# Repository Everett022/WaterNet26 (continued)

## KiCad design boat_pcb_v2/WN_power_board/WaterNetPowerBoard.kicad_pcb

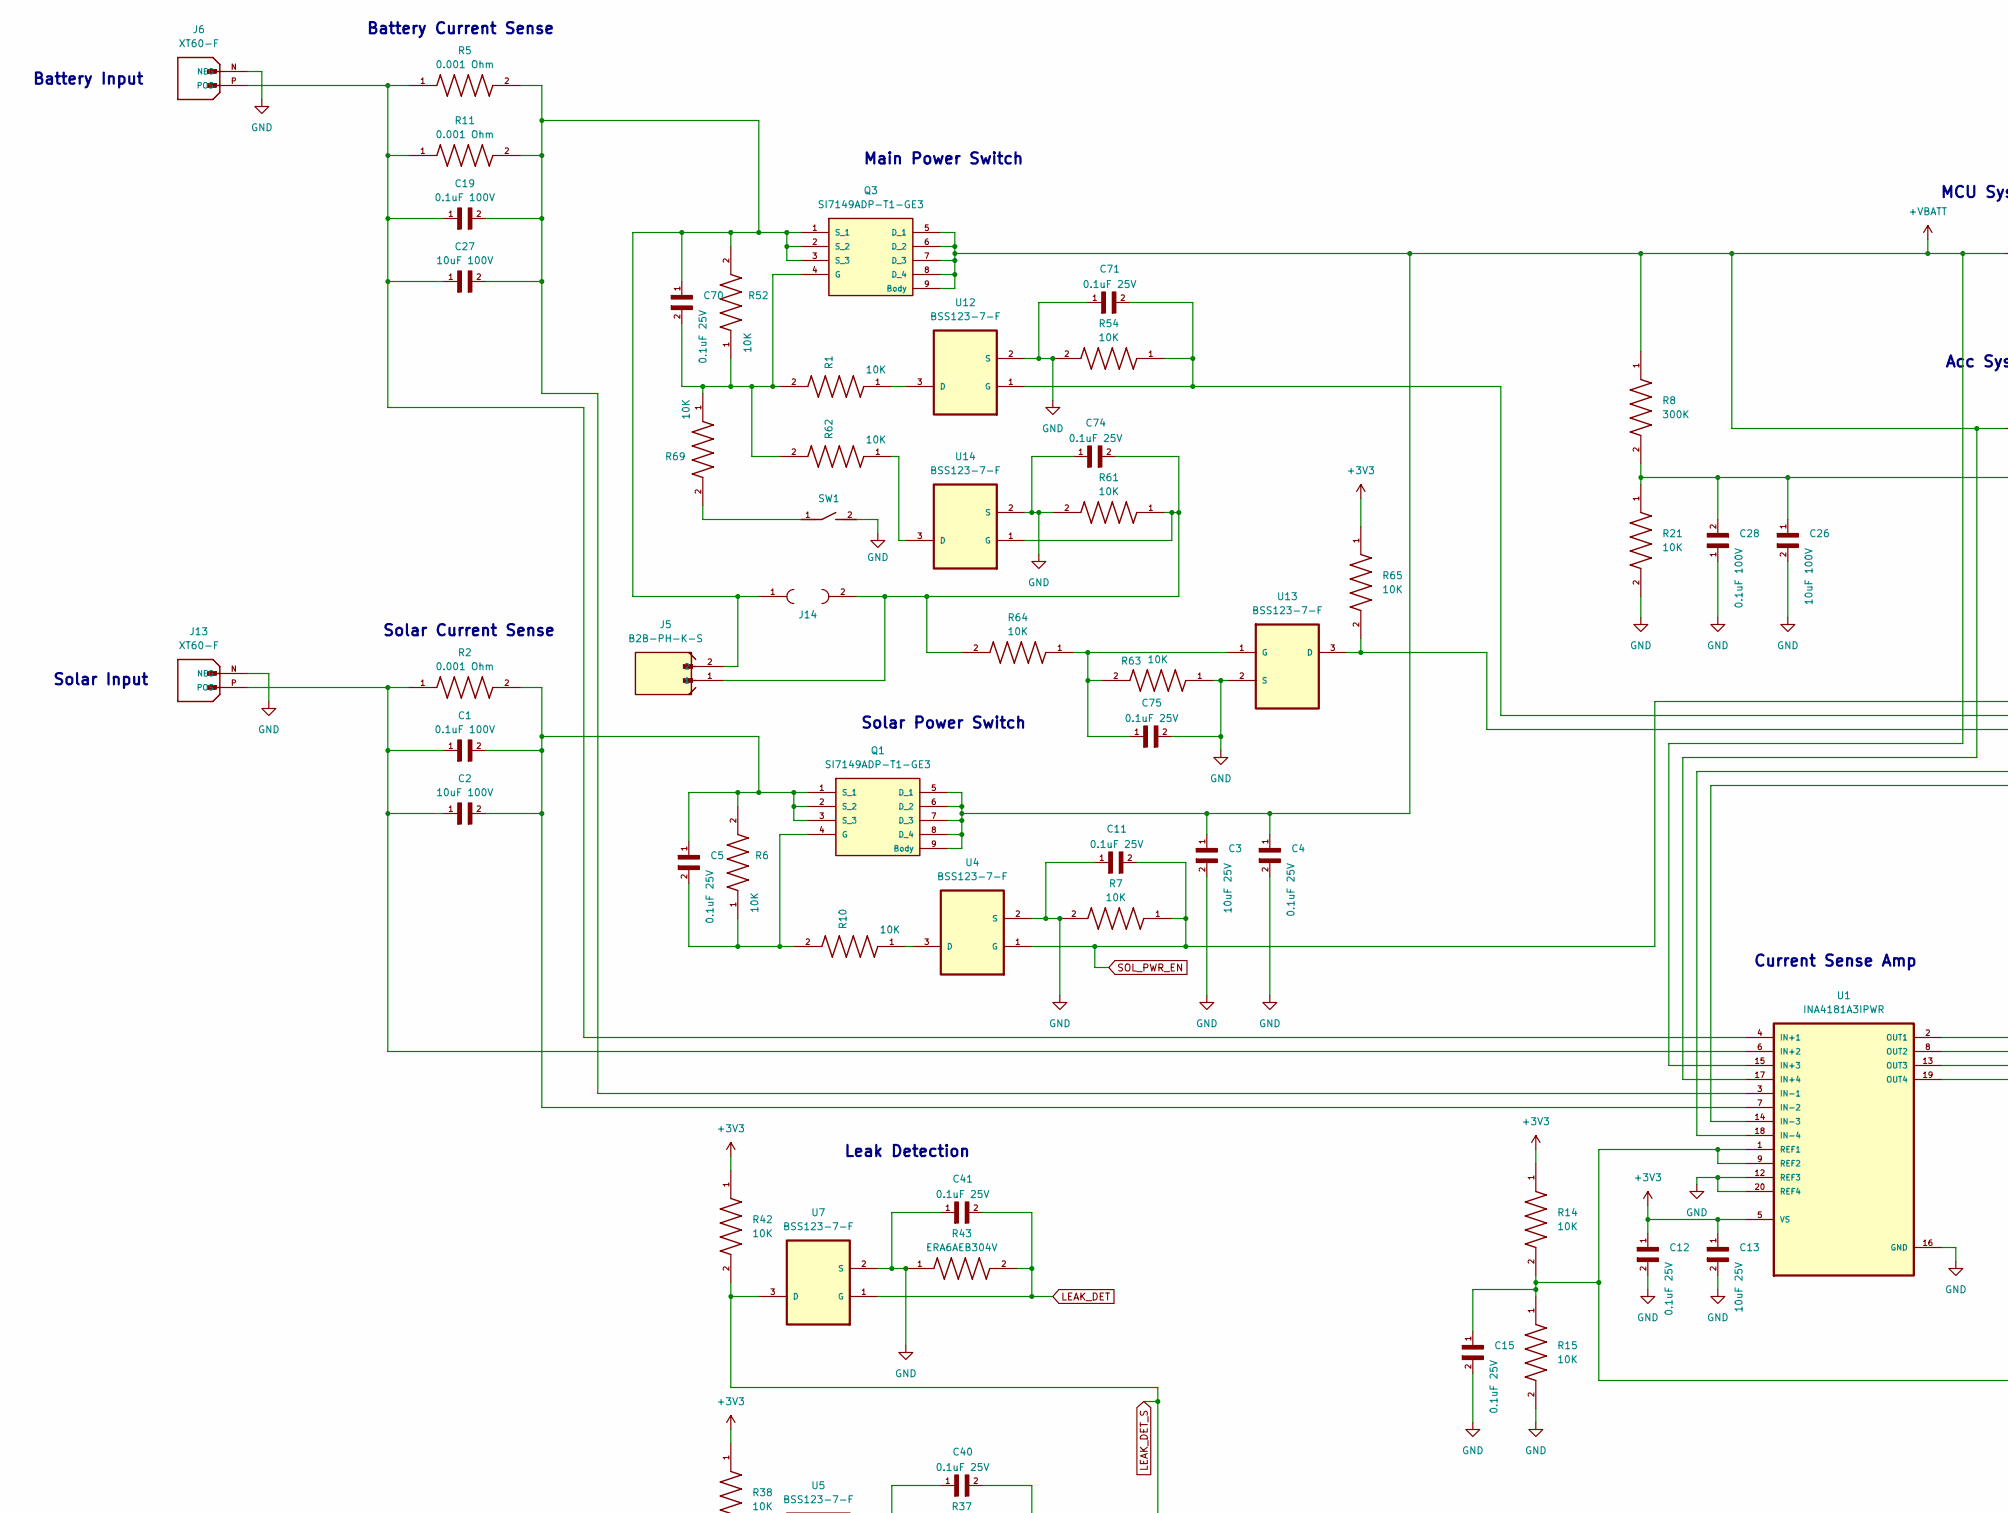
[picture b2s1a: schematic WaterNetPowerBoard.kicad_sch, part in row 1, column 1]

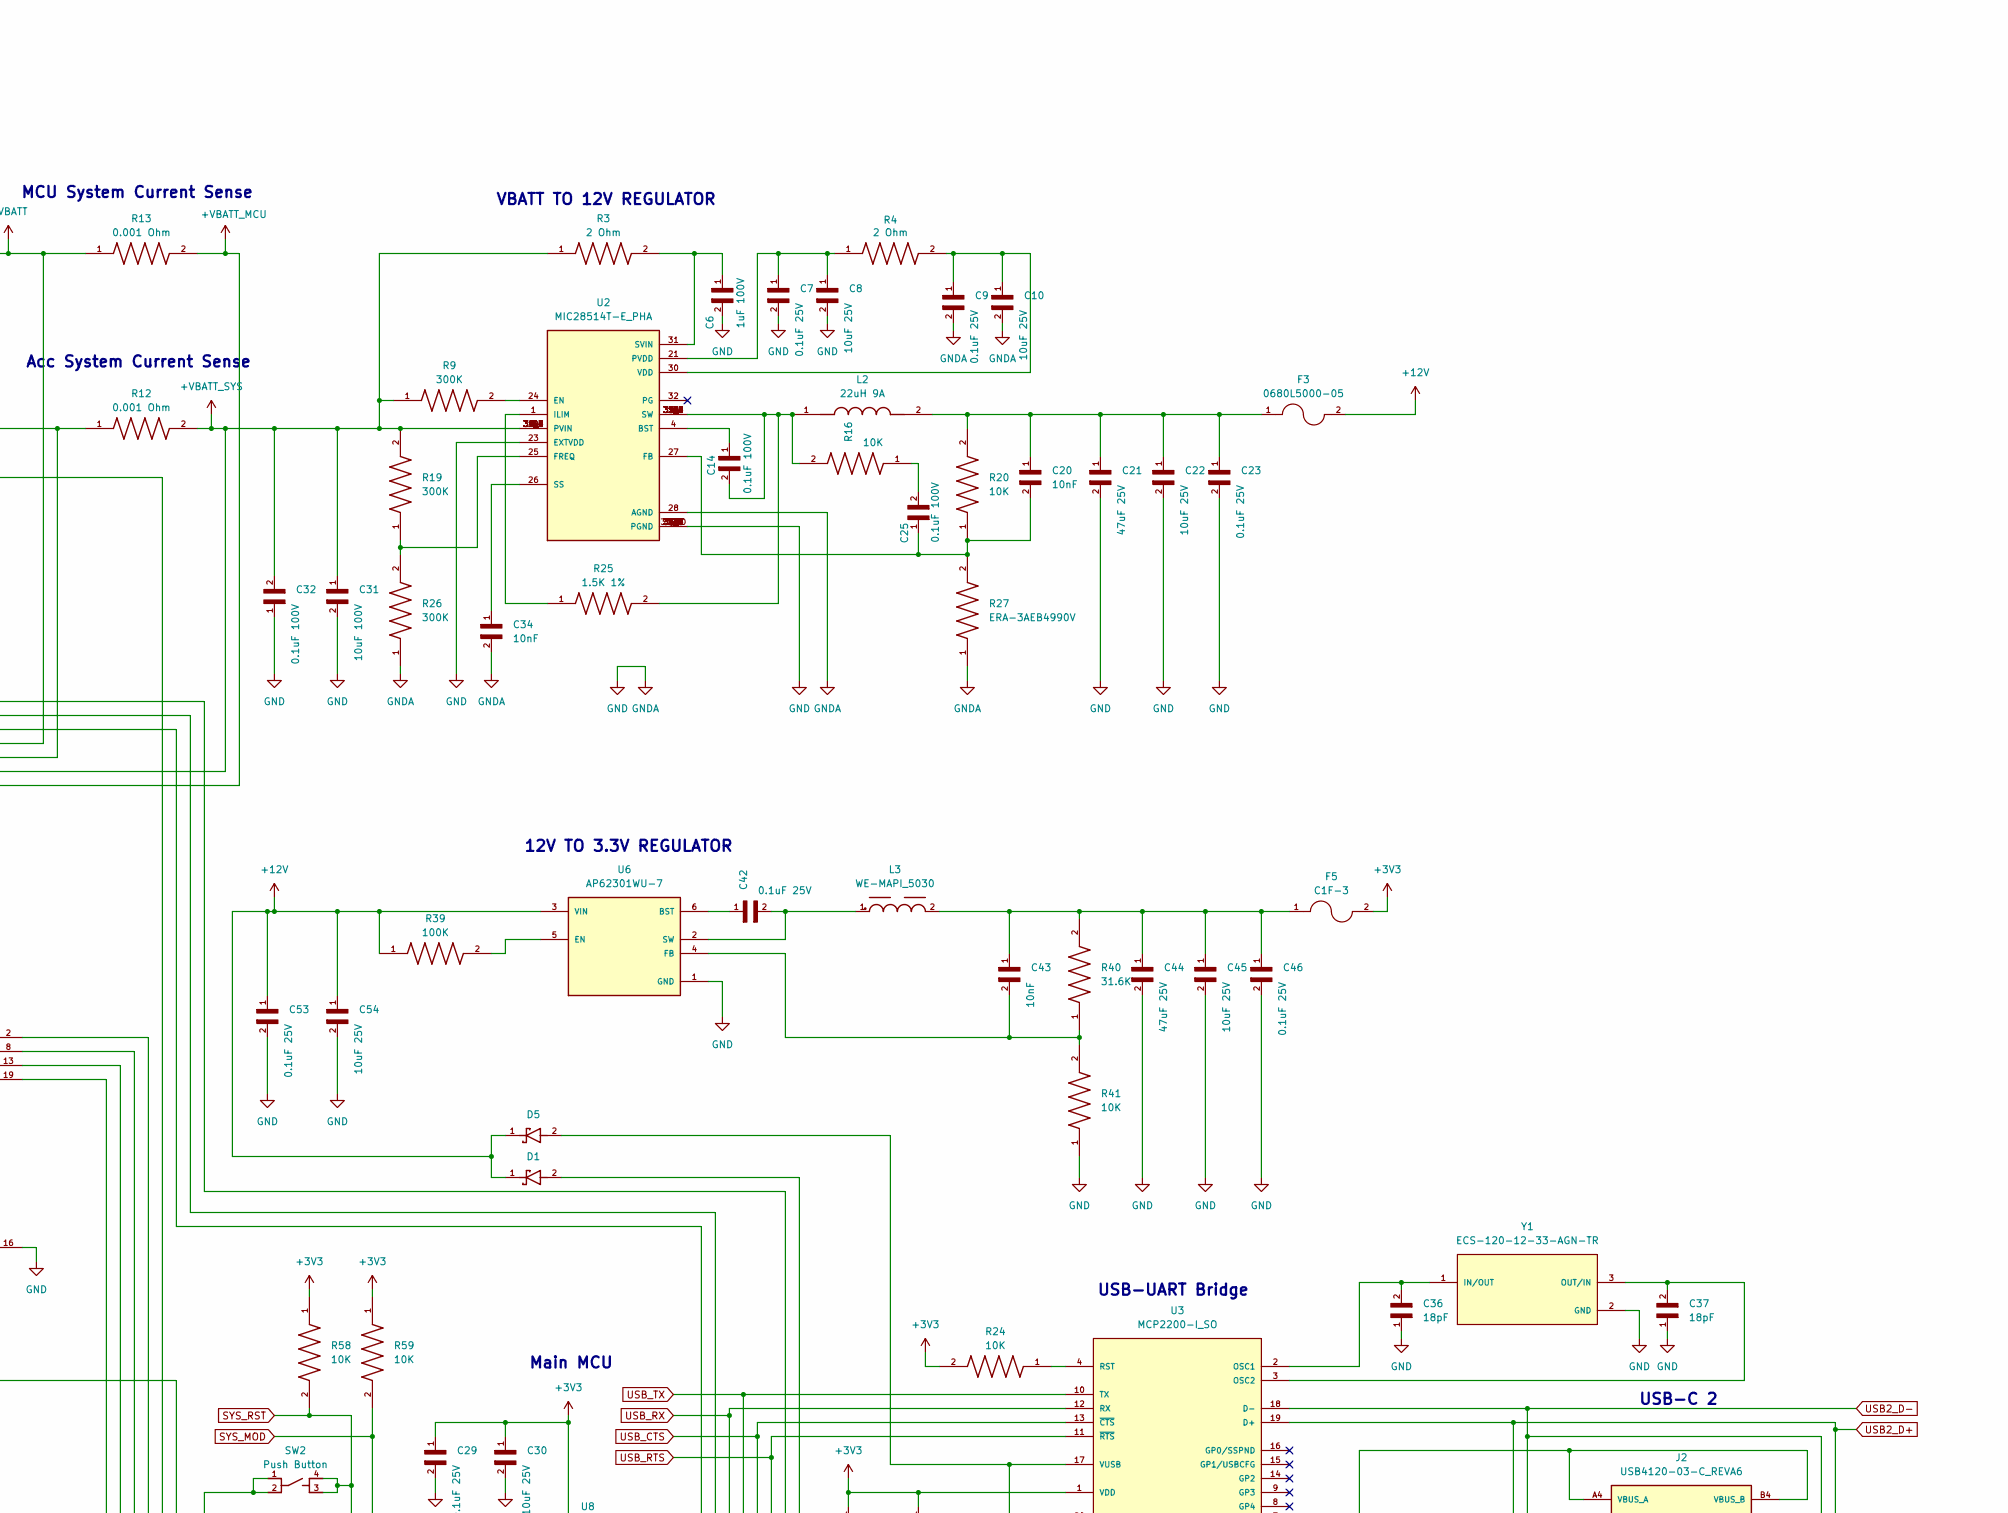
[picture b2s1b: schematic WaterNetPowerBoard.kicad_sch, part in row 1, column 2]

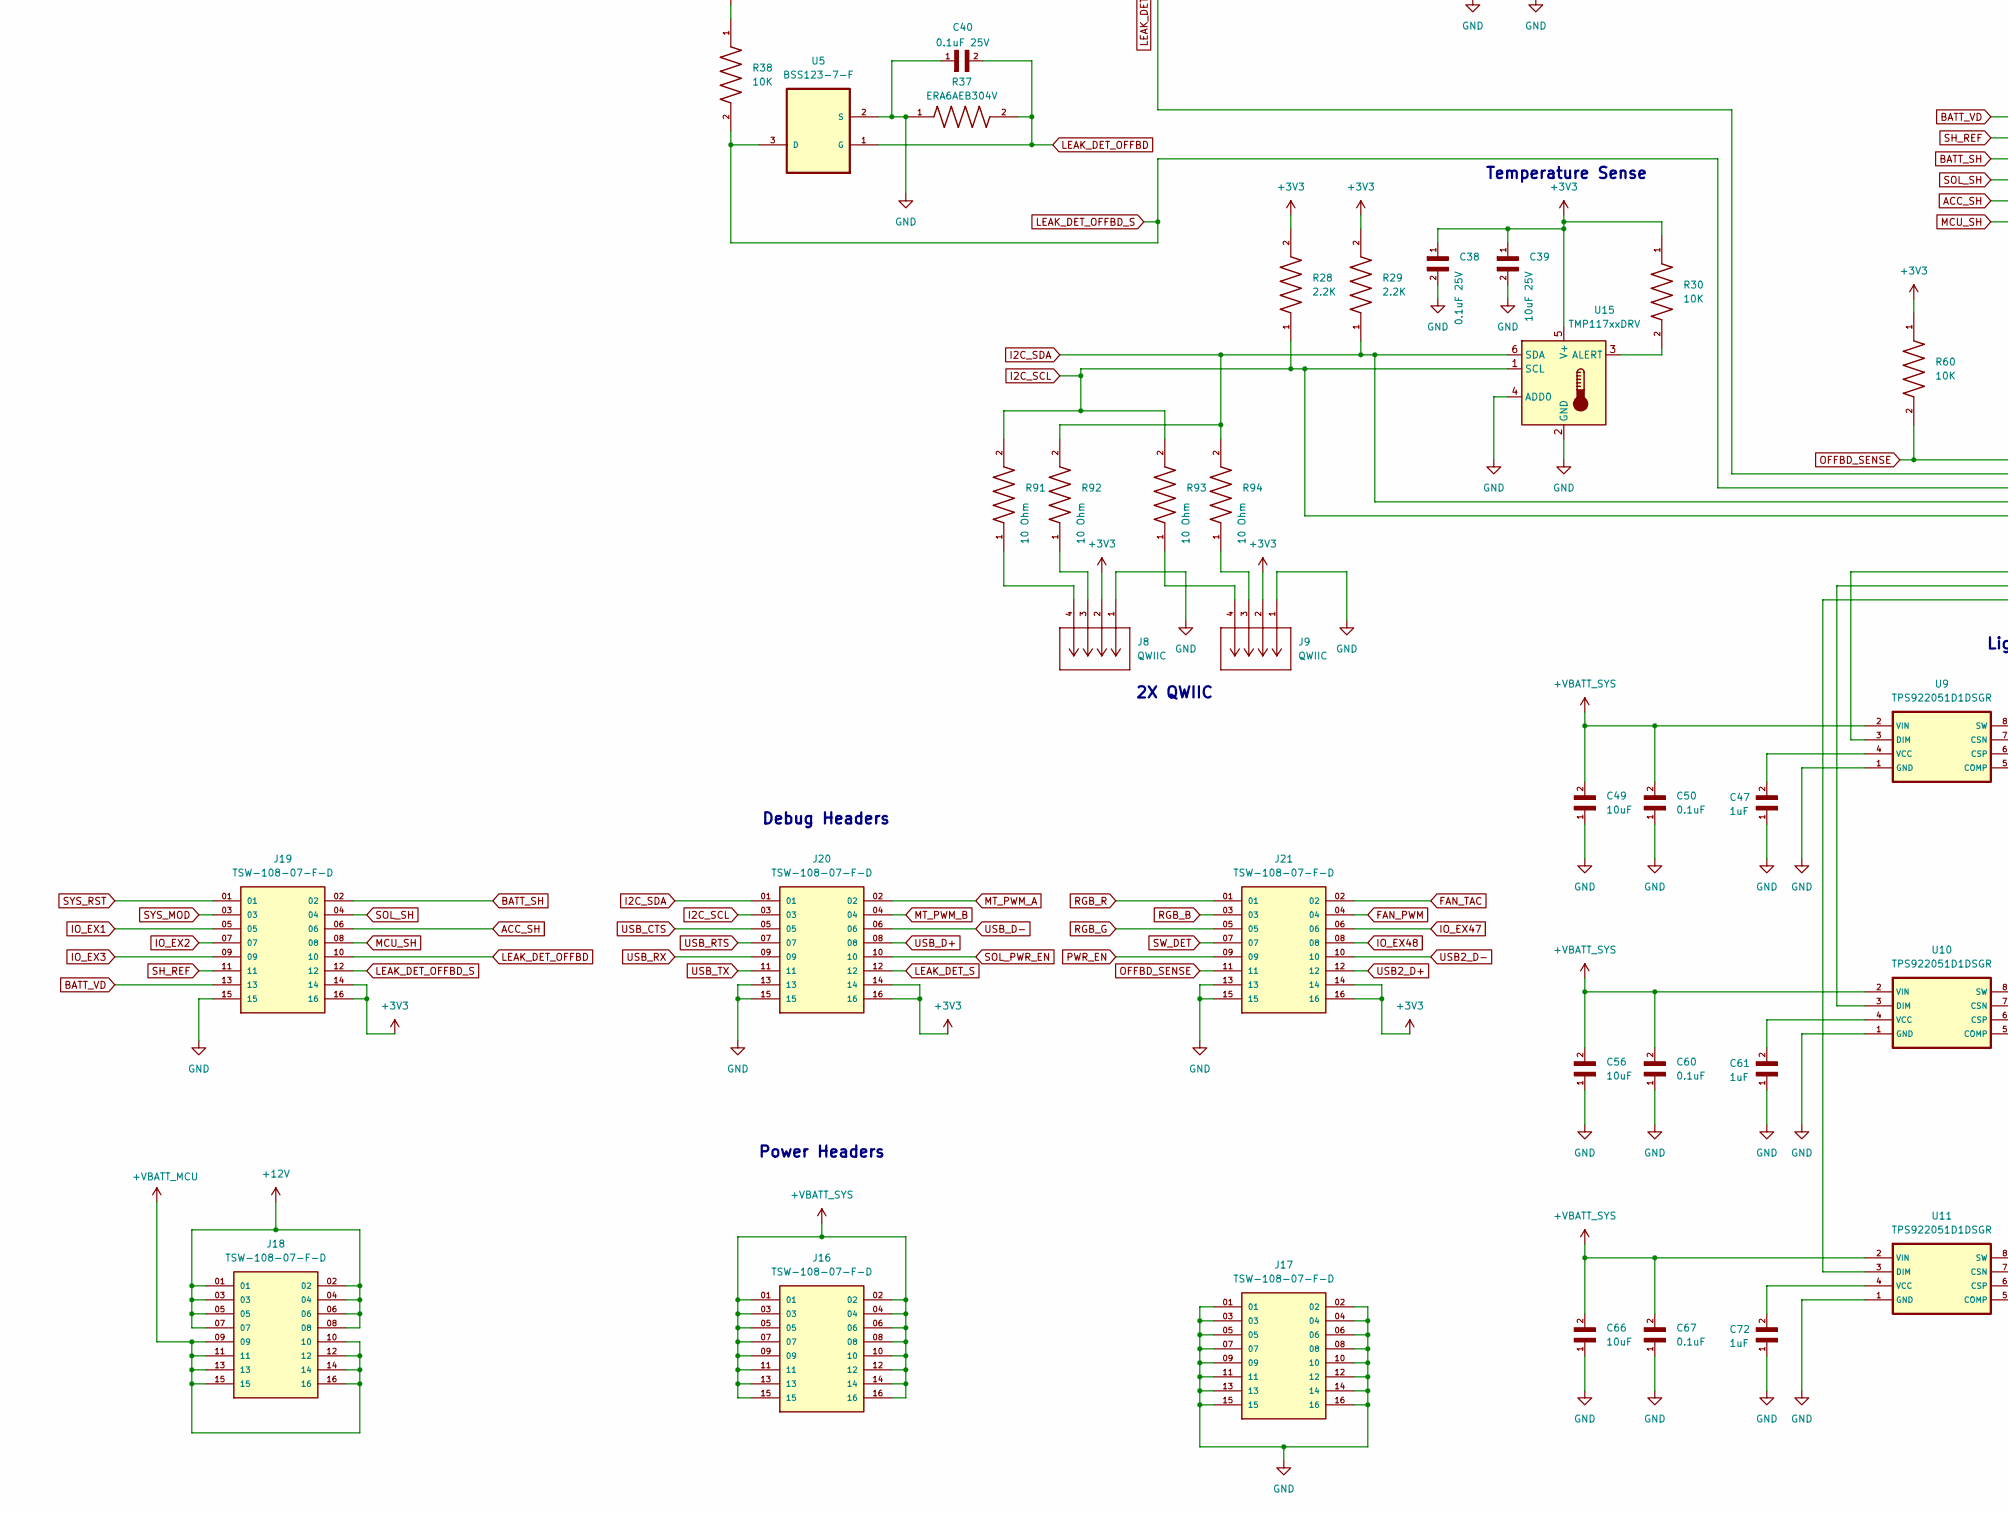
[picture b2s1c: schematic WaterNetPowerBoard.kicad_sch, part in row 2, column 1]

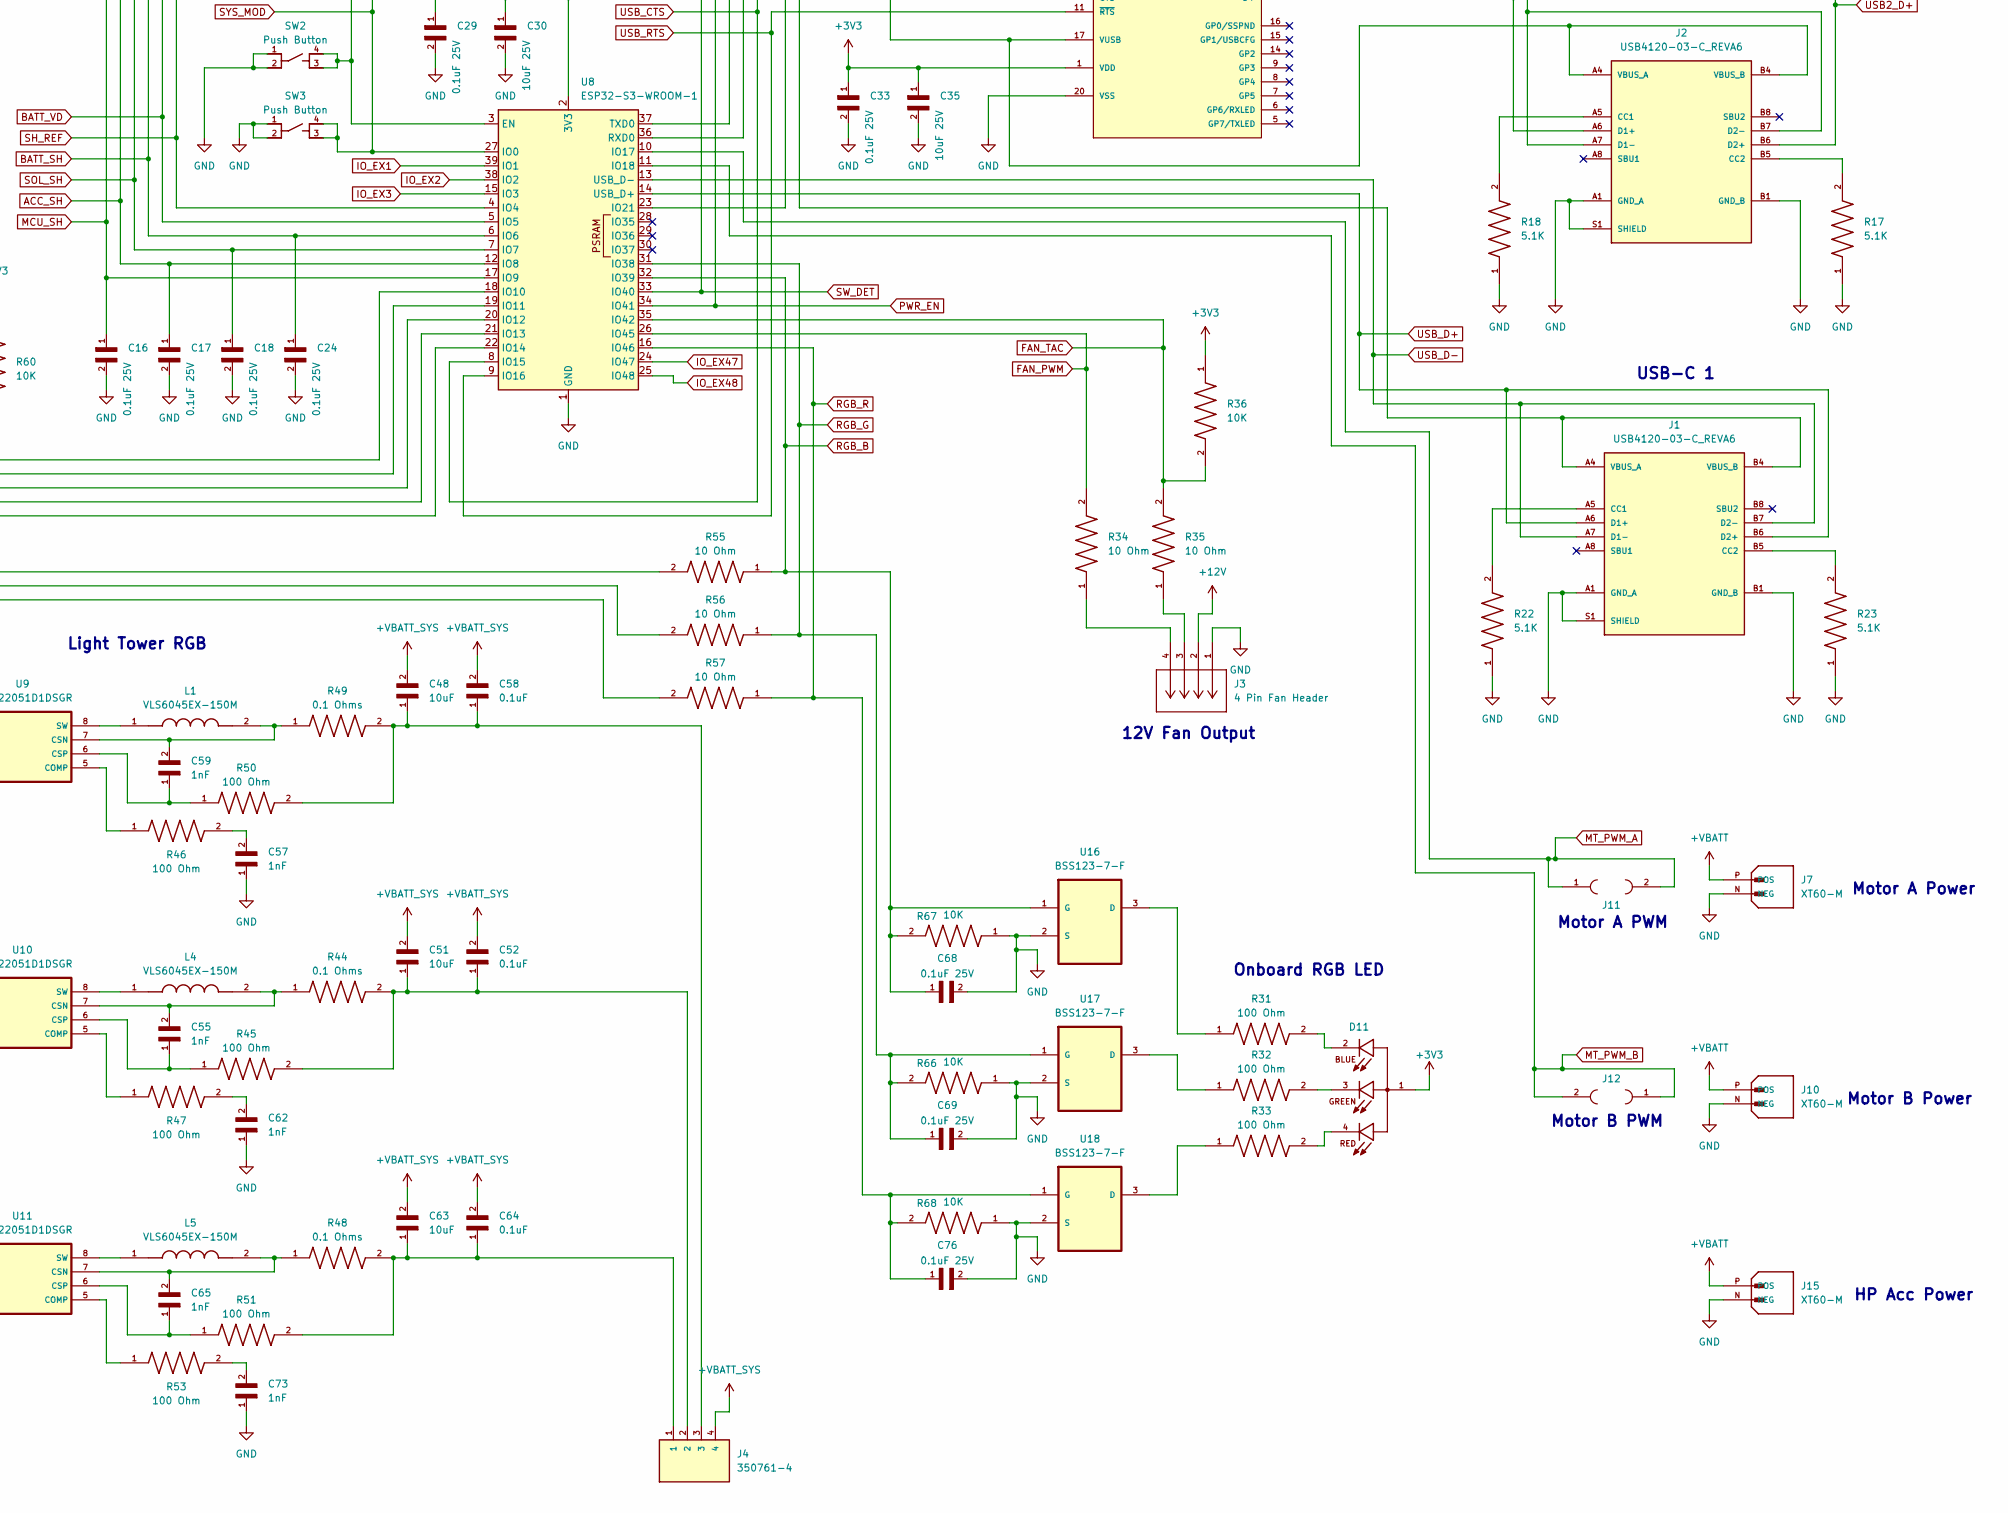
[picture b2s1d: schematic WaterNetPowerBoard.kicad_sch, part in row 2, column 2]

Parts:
C1, C14, C19, C25, C28, C32: 0.1uF 100V; CAPC2012X135N
C2, C26, C27, C31: 10uF 100V; CAPC3225X280N
C3, C8, C10, C13, C22, C30, C35, C39, C45, C54: 10uF 25V; CAPC2012X145N
C4, C5, C7, C9, C11, C12, C15, C16, C17, C18, C23, C24, C29, C33, C38, C40, C41, C42, C46, C53, C68, C69, C70, C71, C74, C75, C76: 0.1uF 25V; CAPC2012X95N
C6: 1uF 100V; CAPC2012X145N
C20, C34, C43: 10nF; CAPC1608X90N
C21, C44: 47uF 25V; CAPC3216X180N
C36, C37: 18pF; CAPC1608X90N
C47, C61, C72: 1uF; CAPC2012X145N
C48, C49, C51, C56, C63, C66: 10uF; CAPC1608X100N
C50, C52, C58, C60, C64, C67: 0.1uF; CAPC1005X55N
C55, C57, C59, C62, C65, C73: 1nF; CAPC1005X55N
D1, D5: RB070MM-30TR; DIO_RB070MM-30TR; PARTREV 003
D11: CLMVC-FKA-CL1D1L71BB7C3C3; LED_CLMVC-FKA-CL1D1L71BB7C3C3; PARTREV 14
F3: 0680L5000-05; FUSC6125X279N; PARTREV 0679H Apr2019
F5: C1F-3; FUSC3215X83N; PARTREV Jan2019
J1, J2: USB4120-03-C_REVA6; GCT_USB4120-03-C_REVA6; PARTREV A6
J3: 4 Pin Fan Header; CONN_SD-47053-001_H10P00_MOL; MANUFACTURER_PART_NUMBER 470531000
J4: 350761-4; TE_350761-4; PART_REV N2
J5: B2B-PH-K-S; JST_B2B-PH-K-S
J6, J13: XT60-F; AMASS_XT60-M; PARTREV V1.2
J7, J10, J15: XT60-M; AMASS_XT60-M; PARTREV V1.2
J8, J9: QWIIC; CONN_SM04B-SRSS-TB_JST; MANUFACTURER_PART_NUMBER SM04B-SRSS-TB
J11, J12, J14: Solderable_100Mil_Jumper
J16, J17, J18, J19, J20, J21: TSW-108-07-F-D; SAMTEC_TSW-108-07-F-D; PARTREV R
L1, L4, L5: VLS6045EX-150M; IND_VLS6045EX-150M; PARTREV N/A
L2: 22uH 9A; ND_SRP1265A-220M; PARTREV 04/20
L3: WE-MAPI_5030
Q1, Q3: SI7149ADP-T1-GE3; POWERPAKSO-8; MOUSER_PART_NUMBER 78-SI7149ADP-T1-GE3
R1, R6, R7, R10, R14, R15, R16, R20, R21, R24, R30, R36, R38, R41, R42, R52, R54, R58, R59, R60, R61, R62, R63, R64, R65, R66, R67, R68, R69: 10K; RES_ERA6AEB103V; PARTREV 3/1/2020
R2, R5, R11: 0.001 Ohm; RESC6864X134N
R3, R4: 2 Ohm; RESC2012X65N
R8, R9, R19, R26: 300K; RES_ERA6AEB304V; PARTREV 3/1/2020
R12, R13: 0.001 Ohm; RESC3216X90N
R17, R18, R22, R23: 5.1K; RESC1508X55N
R25: 1.5K 1%; RES_ERJ3EKF1501V; PARTREV 3/1/2020
R27: ERA-3AEB4990V; RESC1608X55N
R28, R29: 2.2K; RESC1608X55N
R31, R32, R33: 100 Ohm; RES_ERJ3EKF1000V; PARTREV 3/1/2020
R34, R35, R55, R56, R57, R91, R92, R93, R94: 10 Ohm; RESC1508X55N
R37, R43: ERA6AEB304V; RES_ERA6AEB304V; PARTREV 3/1/2020
R39: 100K; RES_ERA6AEB104V; PARTREV 3/1/2020
R40: 31.6K; RES_ERA6AEB3162V; PARTREV 3/1/2020
R44, R48, R49: 0.1 Ohms; RES_ERJ-8BWFR100V
R45, R46, R47, R50, R51, R53: 100 Ohm; RES_ERJ2RKF1000X; PARTREV 3/1/2020
SW1: CS1213AGF160
SW2, SW3: Push Button; SW_PTS810_SJM_250_SMTR_LFS
U1: INA4181A3IPWR; SOP65P640X120-20N
U2: MIC28514T-E_PHA; CONV_MIC28514T-E_PHA; PARTREV E
U3: MCP2200-I_SO; SOIC20; MANUFACTURER_PART_NUMBER mcp2200-i/so
U4, U5, U7, U12, U13, U14, U16, U17, U18: BSS123-7-F; SOT95P240X110-3N; MPN BSS123-7-F
U6: AP62301WU-7; SOT95P280X100-6N; PARTREV Rev. 3 - 2
U8: ESP32-S3-WROOM-1
U9, U10, U11: TPS922051D1DSGR; WSON8_2x2
U15: TMP117xxDRV; WSON-6-1EP_2x2mm_P0.65mm_EP1x1.6mm
Y1: ECS-120-12-33-AGN-TR; XTAL_ECS-120-12-33-AGN-TR

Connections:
+3V3: C12.1, C13.1, C29.1, C30.1, C33.1, C35.1, C38.1, C39.1, D11.1, F5.2, J8.2, J9.2, J19.14, J19.16, J20.14, J20.16, J21.14, J21.16, R14.1, R24.2, R28.2, R29.2, R30.1, R36.1, R38.1, R42.1, R58.1, R59.1, R60.1, R65.1, U1.5 (VS), U3.1 (VDD), U8.2 (3V3), U15.5 (V+)
+12V: C53.1, C54.1, D1.1, D5.1, F3.2, J3.2, J18.01, J18.02, J18.03, J18.04, J18.05, J18.06, J18.07, J18.08, R39.1, U6.3 (VIN)
+VBATT: C3.1, C4.1, J7.P (POS), J10.P (POS), J15.P (POS), Q1.5 (D_1), Q1.6 (D_2), Q1.7 (D_3), Q1.8 (D_4), Q1.9 (Body), Q3.5 (D_1), Q3.6 (D_2), Q3.7 (D_3), Q3.8 (D_4), Q3.9 (Body), R8.1, R12.1, R13.1, U1.15 (IN+3), U1.17 (IN+4)
+VBATT_MCU: J18.09, J18.10, J18.11, J18.12, J18.13, J18.14, J18.15, J18.16, R13.2, U1.14 (IN-3)
+VBATT_SYS: C31.1, C32.2, C48.2, C49.2, C50.2, C51.2, C52.2, C56.2, C58.2, C60.2, C63.2, C64.2, C66.2, C67.2, J4.4, J16.01, J16.02, J16.03, J16.04, J16.05, J16.06, J16.07, J16.08, J16.09, J16.10, J16.11, J16.12, J16.13, J16.14, J16.15, J16.16, R3.1, R9.1, R12.2, R19.2, U1.18 (IN-4), U2.5 (PVIN), U2.6 (PVIN), U2.7 (PVIN), U2.8 (PVIN), U2.9 (PVIN), U2.10 (PVIN), U2.11 (PVIN), U2.34 (PVIN), U2.34_1 (PVIN), U2.34_2 (PVIN), U2.34_3 (PVIN), U2.34_4 (PVIN), U2.34_5 (PVIN), U2.34_6 (PVIN), U9.2 (VIN), U10.2 (VIN), U11.2 (VIN)
ACC_SH: C17.1, J19.06, U1.13 (OUT3), U8.12 (IO8)
BATT_SH: C24.1, J19.02, U1.2 (OUT1), U8.6 (IO6)
BATT_VD: C26.1, C28.2, J19.13, R8.2, R21.1, U8.5 (IO5)
FAN_PWM: J21.04, R34.2, U8.26 (IO45)
FAN_TAC: J21.02, R35.2, R36.2, U8.35 (IO42)
GND: C3.2, C4.2, C6.2, C7.2, C8.2, C9.2, C10.2, C11.1, C12.2, C13.2, C15.2, C16.2, C17.2, C18.2, C21.2, C22.2, C23.2, C24.2, C26.2, C28.1, C29.2, C30.2, C31.2, C32.1, C33.2, C34.2, C35.2, C36.1, C37.1, C38.2, C39.2, C40.1, C41.1, C44.2, C45.2, C46.2, C47.1, C49.1, C50.1, C53.2, C54.2, C56.1, C57.1, C60.1, C61.1, C62.1, C66.1, C67.1, C68.2, C69.2, C71.1, C72.1, C73.1, C74.1, C75.2, C76.2, J1.A1 (GND_A), J1.A12 (GND_A), J1.B1 (GND_B), J1.B12 (GND_B), J1.S1 (SHIELD), J1.S2 (SHIELD), J1.S3 (SHIELD), J1.S4 (SHIELD), J2.A1 (GND_A), J2.A12 (GND_A), J2.B1 (GND_B), J2.B12 (GND_B), J2.S1 (SHIELD), J2.S2 (SHIELD), J2.S3 (SHIELD), J2.S4 (SHIELD), J3.1, J6.N (NEG), J7.N (NEG), J8.1, J9.1, J10.N (NEG), J13.N (NEG), J15.N (NEG), J17.01, J17.02, J17.03, J17.04, J17.05, J17.06, J17.07, J17.08, J17.09, J17.10, J17.11, J17.12, J17.13, J17.14, J17.15, J17.16, J19.15, J20.13, J20.15, J21.13, J21.15, R7.2, R15.2, R17.1, R18.1, R21.2, R22.1, R23.1, R26.1, R27.1, R37.1, R41.1, R43.1, R54.2, R61.2, R63.1, R66.1, R67.1, R68.1, SW1.2, SW2.1, SW2.2, SW3.1, SW3.2, U1.12 (REF3), U1.16 (GND), U1.20 (REF4), U2.2 (PGND), U2.16 (PGND), U2.17 (PGND), U2.18 (PGND), U2.19 (PGND), U2.22 (PGND), U2.23 (EXTVDD), U2.28 (AGND), U2.29 (PGND), U2.33 (PGND), U2.33_1 (PGND), U2.33_2 (PGND), U2.33_3 (PGND), U2.33_4 (PGND), U2.33_5 (PGND), U2.33_6 (PGND), U2.33_7 (PGND), U2.33_8 (PGND), U2.33_9 (PGND), U2.33_10 (PGND), U2.36 (PGND), U2.36_1 (PGND), U2.36_2 (PGND), U3.20 (VSS), U4.2 (S), U5.2 (S), U6.1 (GND), U7.2 (S), U8.1 (GND), U8.40 (GND), U8.41 (GND), U9.1 (GND), U10.1 (GND), U11.1 (GND), U12.2 (S), U13.2 (S), U14.2 (S), U15.2 (GND), U15.4 (ADD0), U16.2 (S), U17.2 (S), U18.2 (S), Y1.2 (GND), Y1.4 (GND)
I2C_SCL: J20.03, R28.1, R91.2, R93.2, U8.22 (IO14), U15.1 (SCL)
I2C_SDA: J20.01, R29.1, R92.2, R94.2, U8.21 (IO13), U15.6 (SDA)
IO_EX1: J19.05, U8.39 (IO1)
IO_EX2: J19.07, U8.38 (IO2)
IO_EX3: J19.09, U8.15 (IO3)
IO_EX47: J21.06, U8.24 (IO47)
IO_EX48: J21.08, U8.25 (IO48)
LEAK_DET: C41.2, R43.2, U7.1 (G)
LEAK_DET_OFFBD: C40.2, J19.10, R37.2, U5.1 (G)
LEAK_DET_OFFBD_S: J19.12, R38.2, U5.3 (D), U8.20 (IO12)
LEAK_DET_S: J20.12, R42.2, U7.3 (D), U8.19 (IO11)
MCU_SH: C16.1, J19.08, U1.19 (OUT4), U8.17 (IO9)
MT_PWM_A: J11.1, J11.2, J20.02, U8.10 (IO17)
MT_PWM_B: J12.1, J12.2, J20.04, U8.11 (IO18)
unnamed: C14.2, L2.1, R16.2, R25.2, U2.3 (SW), U2.12 (SW), U2.13 (SW), U2.14 (SW), U2.15 (SW), U2.20 (SW), U2.35 (SW), U2.35_1 (SW), U2.35_2 (SW), U2.35_3 (SW), U2.35_4 (SW), U2.35_5 (SW), U2.35_6 (SW)
unnamed: C20.1, C21.1, C22.1, C23.1, F3.1, L2.2, R20.2
unnamed: C25.2, R16.1
unnamed: C43.1, C44.1, C45.1, C46.1, F5.1, L3.2, R40.2
unnamed: C48.1, C58.1, J4.3, R49.2, R50.2
unnamed: C51.1, C52.1, J4.2, R44.2, R45.2
unnamed: C57.2, R46.2
unnamed: C62.2, R47.2
unnamed: C63.1, C64.1, J4.1, R48.2, R51.2
unnamed: C73.2, R53.2
unnamed: D11.2, R31.2
unnamed: D11.3, R32.2
unnamed: D11.4, R33.2
unnamed: J1.A5 (CC1), R22.2
unnamed: J1.B5 (CC2), R23.2
unnamed: J2.A5 (CC1), R18.2
unnamed: J2.B5 (CC2), R17.2
unnamed: J3.3, R35.1
unnamed: J3.4, R34.1
unnamed: C19.1, C27.1, J6.P (POS), R5.1, R11.1, U1.4 (IN+1)
unnamed: J8.3, R92.1
unnamed: J8.4, R91.1
unnamed: J9.3, R94.1
unnamed: J9.4, R93.1
unnamed: C1.1, C2.1, J13.P (POS), R2.1, U1.6 (IN+2)
unnamed: C5.2, Q1.4 (G), R6.1, R10.2
unnamed: C1.2, C2.2, C5.1, Q1.1 (S_1), Q1.2 (S_2), Q1.3 (S_3), R2.2, R6.2, U1.7 (IN-2)
unnamed: C70.2, Q3.4 (G), R1.2, R52.1, R62.2, R69.1
unnamed: C19.2, C27.2, C70.1, J5.2, J14.1, Q3.1 (S_1), Q3.2 (S_2), Q3.3 (S_3), R5.2, R11.2, R52.2, U1.3 (IN-1)
unnamed: R69.2, SW1.1
unnamed: C14.1, U2.4 (BST)
unnamed: R9.2, U2.24 (EN)
unnamed: C20.2, C25.1, R20.1, R27.2, U2.27 (FB)
unnamed: R19.1, R26.2, U2.25 (FREQ)
unnamed: R25.1, U2.1 (ILIM)
unnamed: C7.1, C8.1, R4.1, U2.21 (PVDD)
unnamed: C34.1, U2.26 (SS)
unnamed: C6.1, R3.2, U2.31 (SVIN)
unnamed: C9.1, C10.1, R4.2, U2.30 (VDD)
unnamed: C36.2, U3.2 (OSC1), Y1.1 (IN/OUT)
unnamed: C37.2, U3.3 (OSC2), Y1.3 (OUT/IN)
unnamed: R24.1, U3.4 (RST)
unnamed: R10.1, U4.3 (D)
unnamed: C42.1, U6.6 (BST)
unnamed: R39.2, U6.5 (EN)
unnamed: C43.2, R40.1, R41.2, U6.4 (FB)
unnamed: C42.2, L3.1, U6.2 (SW)
unnamed: R46.1, U9.5 (COMP)
unnamed: C59.2, L1.2, R49.1, U9.7 (CSN)
unnamed: C59.1, R50.1, U9.6 (CSP)
unnamed: R55.2, U9.3 (DIM)
unnamed: L1.1, U9.8 (SW)
unnamed: C47.2, U9.4 (VCC)
unnamed: R47.1, U10.5 (COMP)
unnamed: C55.2, L4.2, R44.1, U10.7 (CSN)
unnamed: C55.1, R45.1, U10.6 (CSP)
unnamed: R56.2, U10.3 (DIM)
unnamed: L4.1, U10.8 (SW)
unnamed: C61.2, U10.4 (VCC)
unnamed: R53.1, U11.5 (COMP)
unnamed: C65.2, L5.2, R48.1, U11.7 (CSN)
unnamed: C65.1, R51.1, U11.6 (CSP)
unnamed: R57.2, U11.3 (DIM)
unnamed: L5.1, U11.8 (SW)
unnamed: C72.2, U11.4 (VCC)
unnamed: R1.1, U12.3 (D)
unnamed: C75.1, R63.2, R64.1, U13.1 (G)
unnamed: R62.1, U14.3 (D)
unnamed: C74.2, J5.1, J14.2, R61.1, R64.2, U14.1 (G)
unnamed: R30.2, U15.3 (ALERT)
unnamed: R31.1, U16.3 (D)
unnamed: R32.1, U17.3 (D)
unnamed: R33.1, U18.3 (D)
OFFBD_SENSE: J21.11, R60.2, U8.18 (IO10)
PWR_EN: C71.2, J21.09, R54.1, U8.34 (IO41), U12.1 (G)
RGB_B: C68.1, J21.03, R55.1, R67.2, U8.32 (IO39), U16.1 (G)
RGB_G: C69.1, J21.05, R56.1, R66.2, U8.31 (IO38), U17.1 (G)
RGB_R: C76.1, J21.01, R57.1, R68.2, U8.16 (IO46), U18.1 (G)
SH_REF: C15.1, J19.11, R14.2, R15.1, U1.1 (REF1), U1.9 (REF2), U8.4 (IO4)
SOL_PWR_EN: C11.2, J20.10, R7.1, U4.1 (G), U8.23 (IO21)
SOL_SH: C18.1, J19.04, U1.8 (OUT2), U8.7 (IO7)
SW_DET: J21.07, R65.2, U8.33 (IO40), U13.3 (D)
SYS_MOD: J19.03, R59.2, SW3.3, SW3.4, U8.27 (IO0)
SYS_RST: J19.01, R58.2, SW2.3, SW2.4, U8.3 (EN)
USB2_D+: J2.A6 (D1+), J2.B6 (D2+), J21.12, U3.19 (D+)
USB2_D-: J2.A7 (D1-), J2.B7 (D2-), J21.10, U3.18 (D-)
USB_CTS: J20.05, U3.13 (~CTS), U8.8 (IO15)
USB_D+: J1.A6 (D1+), J1.B6 (D2+), J20.08, U8.14 (USB_D+)
USB_D-: J1.A7 (D1-), J1.B7 (D2-), J20.06, U8.13 (USB_D-)
USB_RTS: J20.07, U3.11 (~RTS), U8.9 (IO16)
USB_RX: J20.09, U3.12 (RX), U8.37 (TXD0)
USB_TX: J20.11, U3.10 (TX), U8.36 (RXD0)

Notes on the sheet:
Solar Power Switch
Main MCU
2X QWIIC
Light Tower RGB
Current Sense Amp
USB-UART Bridge
Main Power Switch
VBATT TO 12V REGULATOR
Motor B PWM
Power Headers
Motor B Power
Debug Headers
HP Acc Power
Motor A PWM
Motor A Power
Acc System Current Sense
MCU System Current Sense
Battery Current Sense
12V TO 3.3V REGULATOR
Battery Input
12V Fan Output
USB-C 1
Onboard RGB LED
Solar Current Sense
Temperature Sense
Solar Input
USB-C 2
Leak Detection

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
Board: 2 copper layers, 203 parts (4 on the bottom side), 117 nets, no tracks yet.
